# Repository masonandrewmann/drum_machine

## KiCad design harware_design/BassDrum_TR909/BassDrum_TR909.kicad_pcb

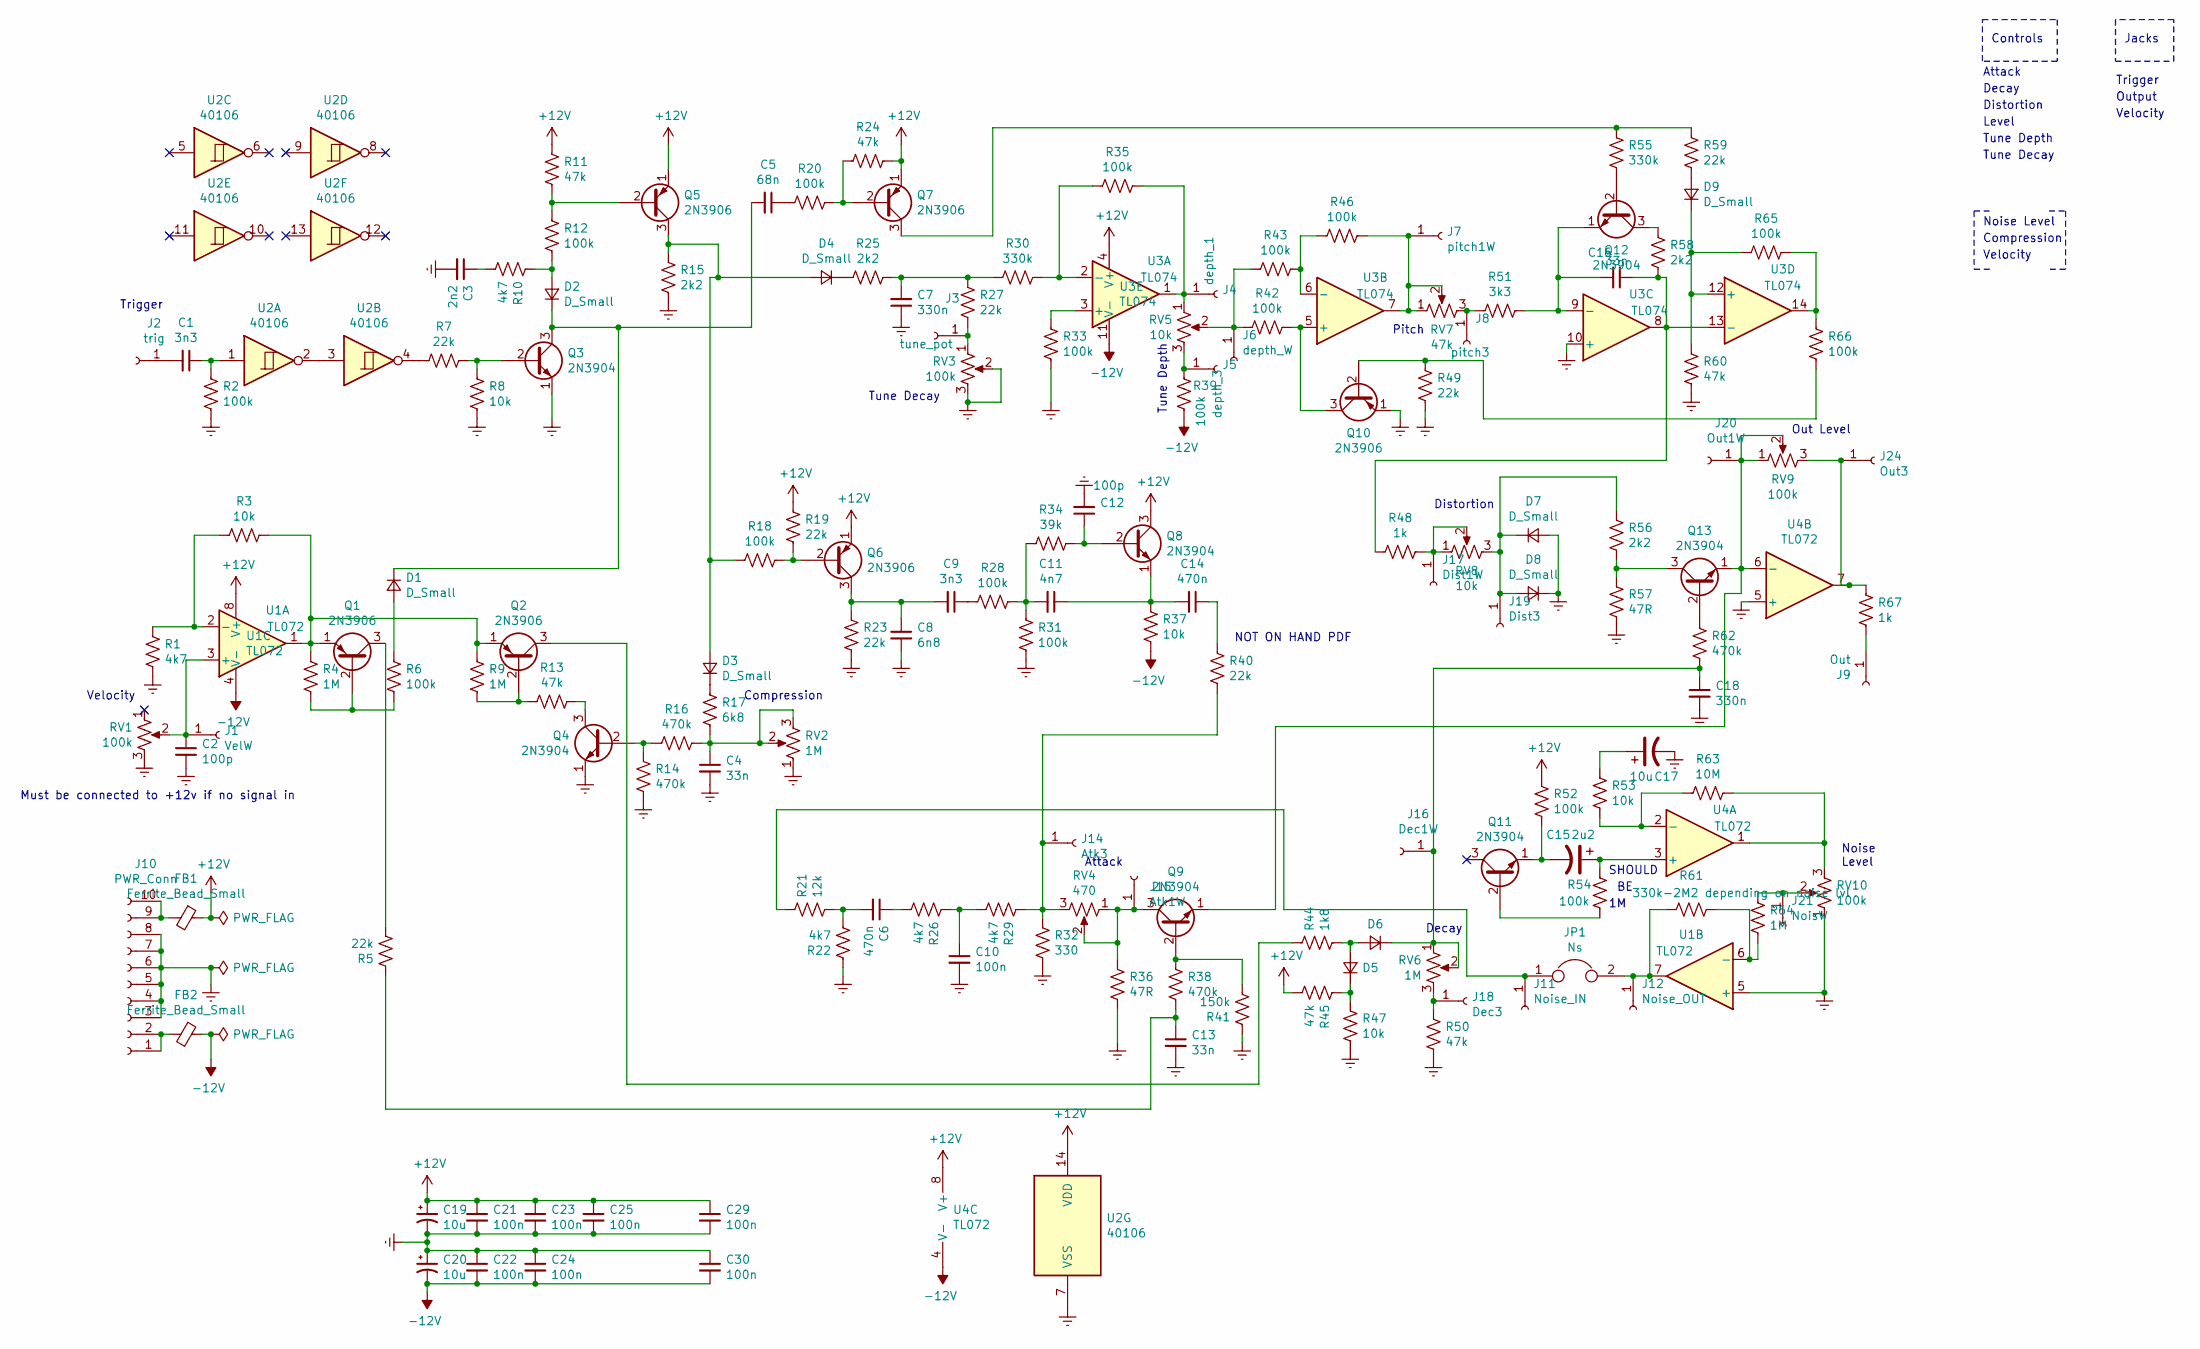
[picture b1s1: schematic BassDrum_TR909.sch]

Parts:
C1, C9: 3n3; C_0603_1608Metric_Pad1.05x0.95mm_HandSolder
C2, C12: 100p; C_0603_1608Metric_Pad1.05x0.95mm_HandSolder
C3: 2n2; C_0603_1608Metric_Pad1.05x0.95mm_HandSolder
C4, C13, C16: 33n; C_0603_1608Metric_Pad1.05x0.95mm_HandSolder
C5: 68n; C_0603_1608Metric_Pad1.05x0.95mm_HandSolder
C6, C14: 470n; C_0603_1608Metric_Pad1.05x0.95mm_HandSolder
C7, C18: 330n; C_0603_1608Metric_Pad1.05x0.95mm_HandSolder
C8: 6n8; C_0603_1608Metric_Pad1.05x0.95mm_HandSolder
C10, C21, C22, C23, C24, C25, C29, C30: 100n; C_0603_1608Metric_Pad1.05x0.95mm_HandSolder
C11: 4n7; C_0603_1608Metric_Pad1.05x0.95mm_HandSolder
C15: 2u2; C_0603_1608Metric_Pad1.05x0.95mm_HandSolder
C17, C19, C20: 10u; CP_Elec_5x5.4
D1, D2, D3, D4, D5, D6, D7, D8, D9: D_Small; D_SOD-323
FB1, FB2: Ferrite_Bead_Small; L_Axial_L7.0mm_D3.3mm_P2.54mm_Vertical_Fastron_MICC
J1: VelW; SolderWirePad_1x01_Drill1mm
J2: trig; SolderWirePad_1x01_Drill1mm
J3: tune_pot; SolderWirePad_1x01_Drill1mm
J4: depth_1; SolderWirePad_1x01_Drill1mm
J5: depth_3; SolderWirePad_1x01_Drill1mm
J6: depth_W; SolderWirePad_1x01_Drill1mm
J7: pitch1W; SolderWirePad_1x01_Drill1mm
J8: pitch3; SolderWirePad_1x01_Drill1mm
J9: Out; SolderWirePad_1x01_Drill1mm
J10: PWR_Conn; IDC-Header_2x05_P2.54mm_Vertical
J11: Noise_IN; SolderWirePad_1x01_Drill1mm
J12: Noise_OUT; SolderWirePad_1x01_Drill1mm
J14: Atk3; SolderWirePad_1x01_Drill1mm
J15: Atk1W; SolderWirePad_1x01_Drill1mm
J16: Dec1W; SolderWirePad_1x01_Drill1mm
J17: Dist1W; SolderWirePad_1x01_Drill1mm
J18: Dec3; SolderWirePad_1x01_Drill1mm
J19: Dist3; SolderWirePad_1x01_Drill1mm
J20: Out1W; SolderWirePad_1x01_Drill1mm
J21: NoisW; SolderWirePad_1x01_Drill1mm
J24: Out3; SolderWirePad_1x01_Drill1mm
JP1: Ns; SolderJumper-2_P1.3mm_Open_RoundedPad1.0x1.5mm
Q1, Q2, Q5, Q6, Q7, Q10: 2N3906; TSOT-23_HandSoldering
Q3, Q4, Q8, Q9, Q11, Q12, Q13: 2N3904; TSOT-23_HandSoldering
R1, R10, R22, R26, R29: 4k7; R_0603_1608Metric_Pad1.05x0.95mm_HandSolder
R2, R6, R12, R18, R20, R28, R31, R33, R35, R39, R42, R43, R46, R52, R54, R65, R66: 100k; R_0603_1608Metric_Pad1.05x0.95mm_HandSolder
R3, R8, R37, R47, R53: 10k; R_0603_1608Metric_Pad1.05x0.95mm_HandSolder
R4, R9, R64: 1M; R_0603_1608Metric_Pad1.05x0.95mm_HandSolder
R5, R7, R19, R23, R27, R40, R49, R59: 22k; R_0603_1608Metric_Pad1.05x0.95mm_HandSolder
R11, R13, R24, R45, R50, R60: 47k; R_0603_1608Metric_Pad1.05x0.95mm_HandSolder
R14, R16, R38, R62: 470k; R_0603_1608Metric_Pad1.05x0.95mm_HandSolder
R15, R25, R56, R58: 2k2; R_0603_1608Metric_Pad1.05x0.95mm_HandSolder
R17: 6k8; R_0603_1608Metric_Pad1.05x0.95mm_HandSolder
R21: 12k; R_0603_1608Metric_Pad1.05x0.95mm_HandSolder
R30, R55: 330k; R_0603_1608Metric_Pad1.05x0.95mm_HandSolder
R32: 330; R_0603_1608Metric_Pad1.05x0.95mm_HandSolder
R34: 39k; R_0603_1608Metric_Pad1.05x0.95mm_HandSolder
R36, R57: 47R; R_0603_1608Metric_Pad1.05x0.95mm_HandSolder
R41: 150k; R_0603_1608Metric_Pad1.05x0.95mm_HandSolder
R44: 1k8; R_0603_1608Metric_Pad1.05x0.95mm_HandSolder
R48, R67: 1k; R_0603_1608Metric_Pad1.05x0.95mm_HandSolder
R51: 3k3; R_0603_1608Metric_Pad1.05x0.95mm_HandSolder
R61: 330k-2M2 depending on noise lvl; R_Axial_DIN0207_L6.3mm_D2.5mm_P7.62mm_Horizontal
R63: 10M; R_0603_1608Metric_Pad1.05x0.95mm_HandSolder
RV1, RV3, RV9: 100k
RV2: 1M; Potentiometer_Runtron_RM-065_Vertical
RV4: 470
RV5, RV8: 10k
RV6: 1M
RV7: 47k
RV10: 100k; Potentiometer_Runtron_RM-065_Vertical
U1, U4: TL072; SOIC-8_3.9x4.9mm_P1.27mm
U2: 40106; SOIC-14_3.9x8.7mm_P1.27mm
U3: TL074; SOIC-14_3.9x8.7mm_P1.27mm

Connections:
+12V: C19.1, C21.1, C23.1, C25.1, C29.1, FB1.1, Q5.1 (E), Q6.1 (E), Q7.1 (E), Q8.3 (C), R11.2, R19.2, R24.2, R45.2, R52.2, U1.8 (V+), U2.14 (VDD), U3.4 (V+), U4.8 (V+)
-12V: C20.2, C22.2, C24.2, C30.2, FB2.1, R37.2, R39.1, U1.4 (V-), U3.11 (V-), U4.4 (V-)
Earth: C2.2, C3.2, C4.2, C7.1, C8.2, C10.2, C12.2, C13.2, C17.2, C18.2, C19.2, C20.1, C21.2, C22.1, C23.2, C24.1, C25.2, C29.2, C30.1, D7.2 (A), D8.1 (K), J10.3, J10.4, J10.5, J10.6, J10.7, J10.8, Q3.1 (E), Q4.1 (E), Q10.1 (E), R1.1, R2.1, R8.1, R14.2, R15.1, R22.1, R23.1, R31.2, R32.2, R33.1, R36.2, R41.1, R47.2, R49.2, R50.2, R57.2, R60.2, RV1.3, RV2.1, RV3.2, RV3.3, RV10.1, U1.5 (+), U2.7 (VSS), U3.10 (+), U4.5 (+)
unnamed: C1.1, R2.2, U2.1
unnamed: C1.2, J2.1
unnamed: C2.1, J1.1, RV1.2, U1.3 (+)
unnamed: C3.1, R10.1
unnamed: C4.1, R16.1, R17.1, RV2.2, RV2.3
unnamed: C5.1, R20.1
unnamed: C5.2, D1.1 (K), D2.1 (K), Q3.3 (C)
unnamed: C6.1, R26.2
unnamed: C6.2, R21.2, R22.2
unnamed: C7.2, R25.2, R27.1, R30.2
unnamed: C8.1, C9.2, Q6.3 (C), R23.2
unnamed: C9.1, R28.1
unnamed: C10.1, R26.1, R29.2
unnamed: C11.1, C14.2, Q8.1 (E), R37.1
unnamed: C11.2, R28.2, R31.1, R34.1
unnamed: C12.1, Q8.2 (B), R34.2
unnamed: C13.1, R5.1, R38.2
unnamed: C14.1, R40.1
unnamed: C15.1, R54.2, U4.3 (+)
unnamed: C15.2, Q11.1 (E), R52.1
unnamed: C16.1, R48.1, R58.2, U3.8, U3.13 (-)
unnamed: C16.2, Q12.1 (E), R51.2, U3.9 (-)
unnamed: C17.1, R53.2
unnamed: C18.1, D6.1 (K), J16.1, R62.2, RV6.1, RV6.2
unnamed: D1.2 (A), R6.2
unnamed: D2.2 (A), R10.2, R12.1
unnamed: D3.1 (K), R17.2
unnamed: D3.2 (A), D4.2 (A), Q5.3 (C), R15.2, R18.2
unnamed: D4.1 (K), R25.1
unnamed: D5.1 (K), R45.1, R47.1
unnamed: D5.2 (A), D6.2 (A), R44.2
unnamed: D7.1 (K), D8.2 (A), J19.1, R56.1, RV8.3
unnamed: D9.1 (K), R60.1, R65.2, U3.12 (+)
unnamed: D9.2 (A), R59.2
unnamed: FB1.2, J10.9, J10.10
unnamed: FB2.2, J10.1, J10.2
unnamed: J3.1, R27.2, RV3.1
unnamed: J4.1, R35.1, RV5.1, U3.1
unnamed: J5.1, R39.2, RV5.3
unnamed: J6.1, R42.1, R43.1, RV5.2
unnamed: J7.1, R46.2, RV7.1, RV7.2, U3.7
unnamed: J8.1, R51.1, RV7.3
unnamed: J9.1, R67.2
unnamed: J11.1, JP1.1, R21.1
unnamed: J12.1, JP1.2, R61.1, U1.7
unnamed: J14.1, R29.1, R32.1, R40.2, RV4.3
unnamed: J15.1, Q9.3 (C), R36.1, RV4.1, RV4.2
unnamed: J17.1, R48.2, RV8.1, RV8.2
unnamed: J18.1, R50.1, RV6.3
unnamed: J20.1, Q9.1 (E), Q13.1 (E), RV9.1, RV9.2, U4.6 (-)
unnamed: J21.1, R64.2, RV10.2
unnamed: J24.1, R67.1, RV9.3, U4.7
unnamed: Q1.1 (E), Q2.1 (E), R3.1, R4.2, R9.2, U1.1
unnamed: Q1.2 (B), R4.1, R6.1
unnamed: Q1.3 (C), R5.2
unnamed: Q2.2 (B), R9.1, R13.1
unnamed: Q2.3 (C), R44.1
unnamed: Q3.2 (B), R7.1, R8.2
unnamed: Q4.2 (B), R14.1, R16.2
unnamed: Q4.3 (C), R13.2
unnamed: Q5.2 (B), R11.1, R12.2
unnamed: Q6.2 (B), R18.1, R19.1
unnamed: Q7.2 (B), R20.2, R24.1
unnamed: Q7.3 (C), R55.1, R59.1
unnamed: Q9.2 (B), R38.1, R41.2
unnamed: Q10.2 (B), R49.1, R66.1
unnamed: Q10.3 (C), R42.2, U3.5 (+)
unnamed: Q11.2 (B), R54.1
unnamed: Q12.2 (B), R55.2
unnamed: Q12.3 (C), R58.1
unnamed: Q13.2 (B), R62.1
unnamed: Q13.3 (C), R56.2, R57.1
unnamed: R1.2, R3.2, U1.2 (-)
unnamed: R7.2, U2.4
unnamed: R30.1, R35.2, U3.2 (-)
unnamed: R33.2, U3.3 (+)
unnamed: R43.2, R46.1, U3.6 (-)
unnamed: R53.1, R63.2, U4.2 (-)
unnamed: R61.2, R64.1, U1.6 (-)
unnamed: R63.1, RV10.3, U4.1
unnamed: R65.1, R66.2, U3.14
unnamed: U2.2, U2.3

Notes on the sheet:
Tune Decay
Tune Depth
Pitch
Distortion
Out Level
Compression
Attack
Decay
Noise Level
Velocity
Trigger
Must be connected to +12v if no signal in
NOT ON HAND PDF
Controls
Attack
Decay
Distortion
Level
Tune Decay
Noise Level
Jacks
Output
SHOULD

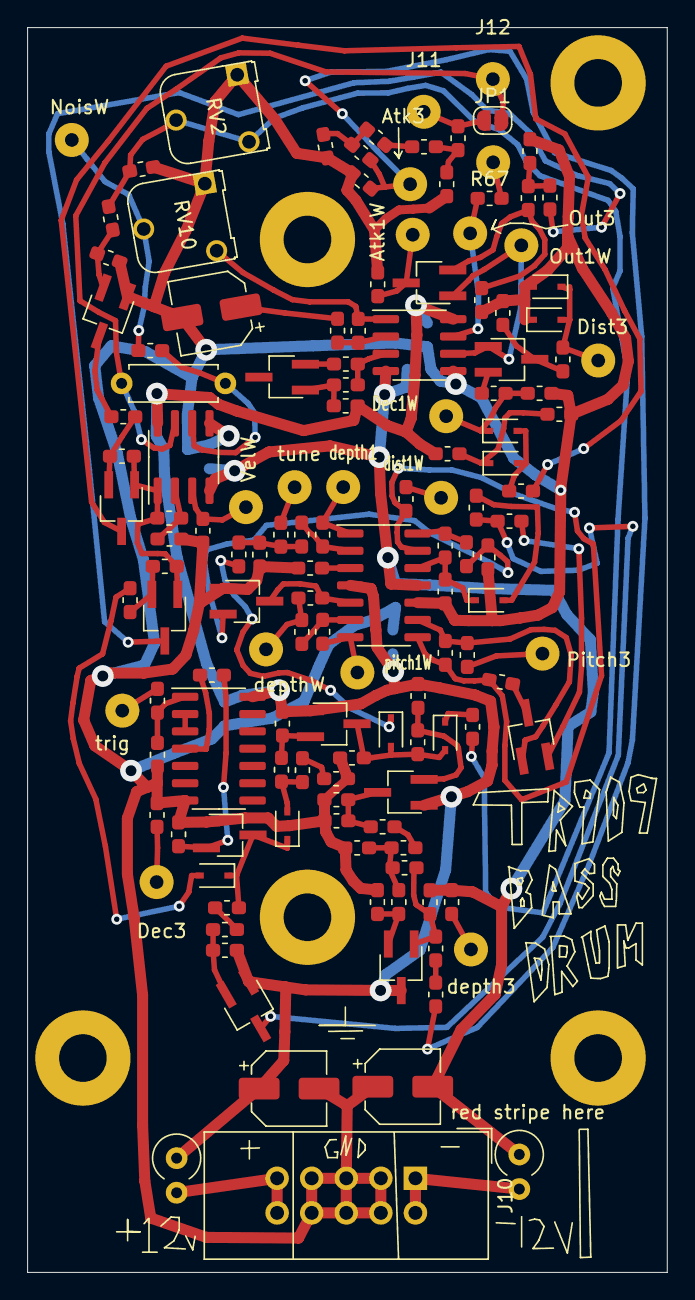
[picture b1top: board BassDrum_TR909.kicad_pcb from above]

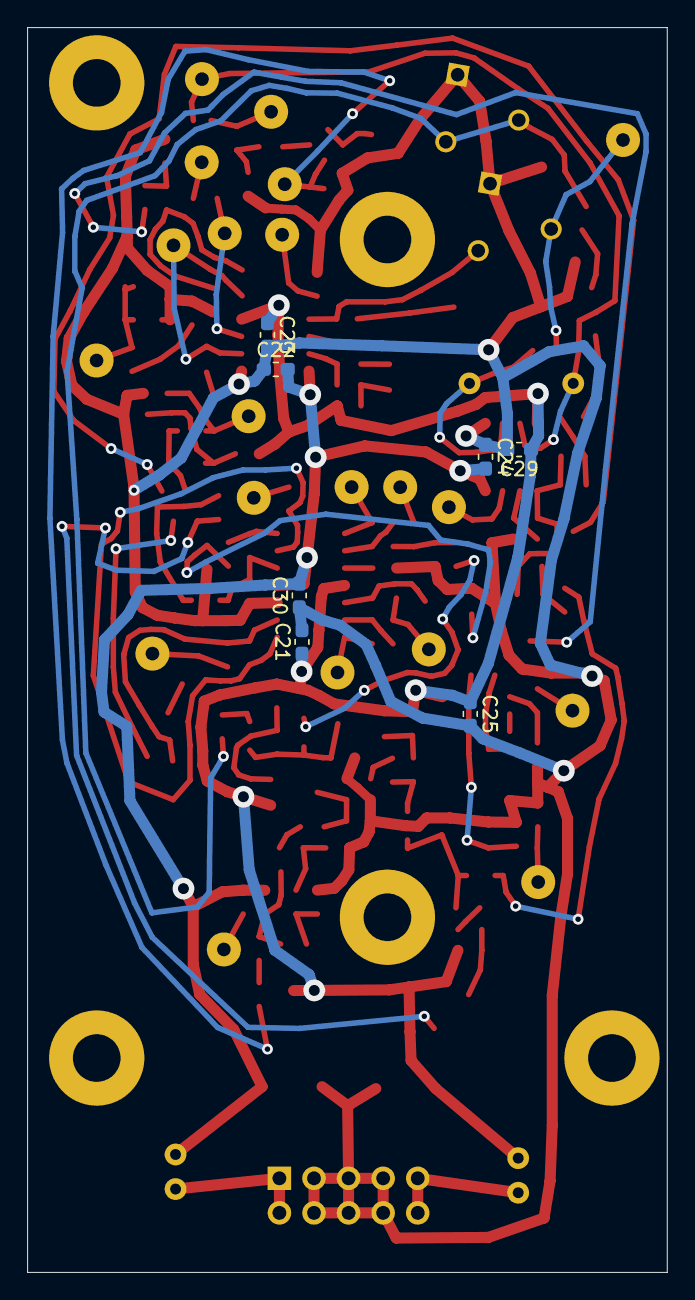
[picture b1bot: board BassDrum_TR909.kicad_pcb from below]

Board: 2 copper layers, 47.0 x 91.4 mm, 146 parts (7 on the bottom side), 85 nets.

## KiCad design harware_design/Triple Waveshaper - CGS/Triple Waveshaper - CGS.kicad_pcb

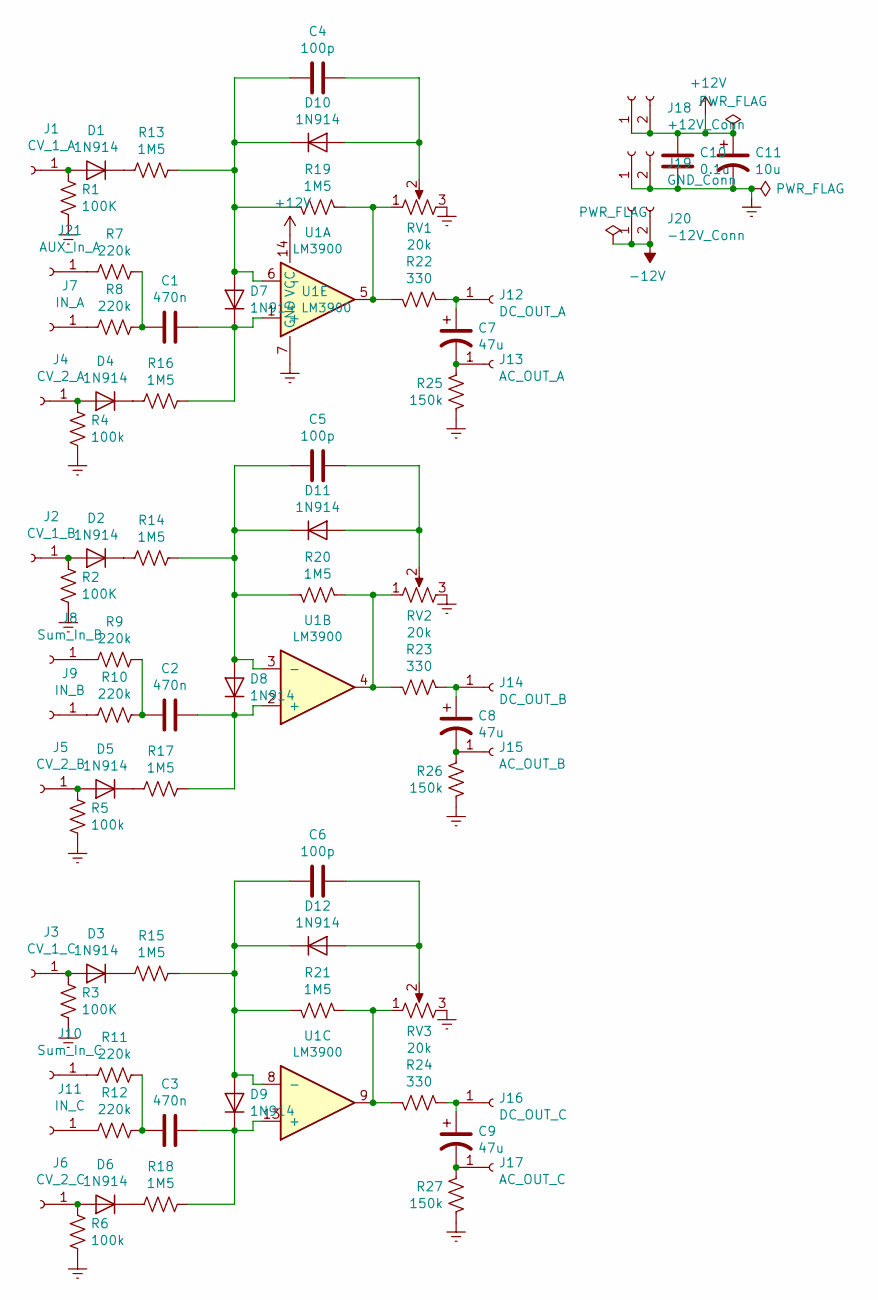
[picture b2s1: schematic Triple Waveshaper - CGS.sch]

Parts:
C1, C2, C3: 470n; C_Rect_L7.0mm_W2.5mm_P5.00mm
C4, C5, C6: 100p; C_Rect_L7.0mm_W2.5mm_P5.00mm
C7, C8, C9: 47u; CP_Radial_D4.0mm_P2.00mm
C10: 0.1u; C_Rect_L7.0mm_W2.5mm_P5.00mm
C11: 10u; CP_Radial_D4.0mm_P2.00mm
D1, D2, D3, D4, D5, D6, D7, D8, D9, D10, D11, D12: 1N914; D_T-1_P5.08mm_Horizontal
J1: CV_1_A; SolderWirePad_1x01_Drill1mm
J2: CV_1_B; SolderWirePad_1x01_Drill1mm
J3: CV_1_C; SolderWirePad_1x01_Drill1mm
J4: CV_2_A; SolderWirePad_1x01_Drill1mm
J5: CV_2_B; SolderWirePad_1x01_Drill1mm
J6: CV_2_C; SolderWirePad_1x01_Drill1mm
J7: IN_A; SolderWirePad_1x01_Drill1mm
J8: Sum_In_B; SolderWirePad_1x01_Drill1mm
J9: IN_B; SolderWirePad_1x01_Drill1mm
J10: Sum_In_C; SolderWirePad_1x01_Drill1mm
J11: IN_C; SolderWirePad_1x01_Drill1mm
J12: DC_OUT_A; SolderWirePad_1x01_Drill1mm
J13: AC_OUT_A; SolderWirePad_1x01_Drill1mm
J14: DC_OUT_B; SolderWirePad_1x01_Drill1mm
J15: AC_OUT_B; SolderWirePad_1x01_Drill1mm
J16: DC_OUT_C; SolderWirePad_1x01_Drill1mm
J17: AC_OUT_C; SolderWirePad_1x01_Drill1mm
J18: +12V_Conn; SolderWirePad_1x02_P3.81mm_Drill1mm
J19: GND_Conn; SolderWirePad_1x02_P3.81mm_Drill1mm
J20: -12V_Conn; SolderWirePad_1x02_P3.81mm_Drill1mm
J21: AUX_In_A; SolderWirePad_1x01_Drill1mm
R1, R2, R3: 100K; R_Axial_DIN0207_L6.3mm_D2.5mm_P7.62mm_Horizontal
R4, R5, R6: 100k; R_Axial_DIN0207_L6.3mm_D2.5mm_P7.62mm_Horizontal
R7, R8, R9, R10, R11, R12: 220k; R_Axial_DIN0207_L6.3mm_D2.5mm_P7.62mm_Horizontal
R13, R14, R15, R16, R17, R18, R19, R20, R21: 1M5; R_Axial_DIN0207_L6.3mm_D2.5mm_P7.62mm_Horizontal
R22, R23, R24: 330; R_Axial_DIN0207_L6.3mm_D2.5mm_P7.62mm_Horizontal
R25, R26, R27: 150k; R_Axial_DIN0207_L6.3mm_D2.5mm_P7.62mm_Horizontal
RV1, RV2, RV3: 20k; Potentiometer_Runtron_RM-065_Vertical
U1: LM3900; DIP-14_W7.62mm_Socket

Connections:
+12V: C10.1, C11.1, J18.1, J18.2, U1.14 (VCC)
-12V: J20.1, J20.2
Earth: C10.2, C11.2, J19.1, J19.2, R1.1, R2.1, R3.1, R4.1, R5.1, R6.1, R25.1, R26.1, R27.1, RV1.3, RV2.3, RV3.3, U1.7 (GND)
unnamed: C1.1, R7.1, R8.1
unnamed: C1.2, D7.1 (K), R16.1, U1.1 (+)
unnamed: C2.1, R9.1, R10.1
unnamed: C2.2, D8.1 (K), R17.1, U1.2 (+)
unnamed: C3.1, R11.1, R12.1
unnamed: C3.2, D9.1 (K), R18.1, U1.13 (+)
unnamed: C4.1, D7.2 (A), D10.1 (K), R13.1, R19.2, U1.6 (-)
unnamed: C4.2, D10.2 (A), RV1.2
unnamed: C5.1, D8.2 (A), D11.1 (K), R14.1, R20.2, U1.3 (-)
unnamed: C5.2, D11.2 (A), RV2.2
unnamed: C6.1, D9.2 (A), D12.1 (K), R15.1, R21.2, U1.8 (-)
unnamed: C6.2, D12.2 (A), RV3.2
unnamed: C7.1, J12.1, R22.1
unnamed: C7.2, J13.1, R25.2
unnamed: C8.1, J14.1, R23.1
unnamed: C8.2, J15.1, R26.2
unnamed: C9.1, J16.1, R24.1
unnamed: C9.2, J17.1, R27.2
unnamed: D1.1 (K), R13.2
unnamed: D1.2 (A), J1.1, R1.2
unnamed: D2.1 (K), R14.2
unnamed: D2.2 (A), J2.1, R2.2
unnamed: D3.1 (K), R15.2
unnamed: D3.2 (A), J3.1, R3.2
unnamed: D4.1 (K), R16.2
unnamed: D4.2 (A), J4.1, R4.2
unnamed: D5.1 (K), R17.2
unnamed: D5.2 (A), J5.1, R5.2
unnamed: D6.1 (K), R18.2
unnamed: D6.2 (A), J6.1, R6.2
unnamed: J7.1, R8.2
unnamed: J8.1, R9.2
unnamed: J9.1, R10.2
unnamed: J10.1, R11.2
unnamed: J11.1, R12.2
unnamed: J21.1, R7.2
unnamed: R19.1, R22.2, RV1.1, U1.5
unnamed: R20.1, R23.2, RV2.1, U1.4
unnamed: R21.1, R24.2, RV3.1, U1.9

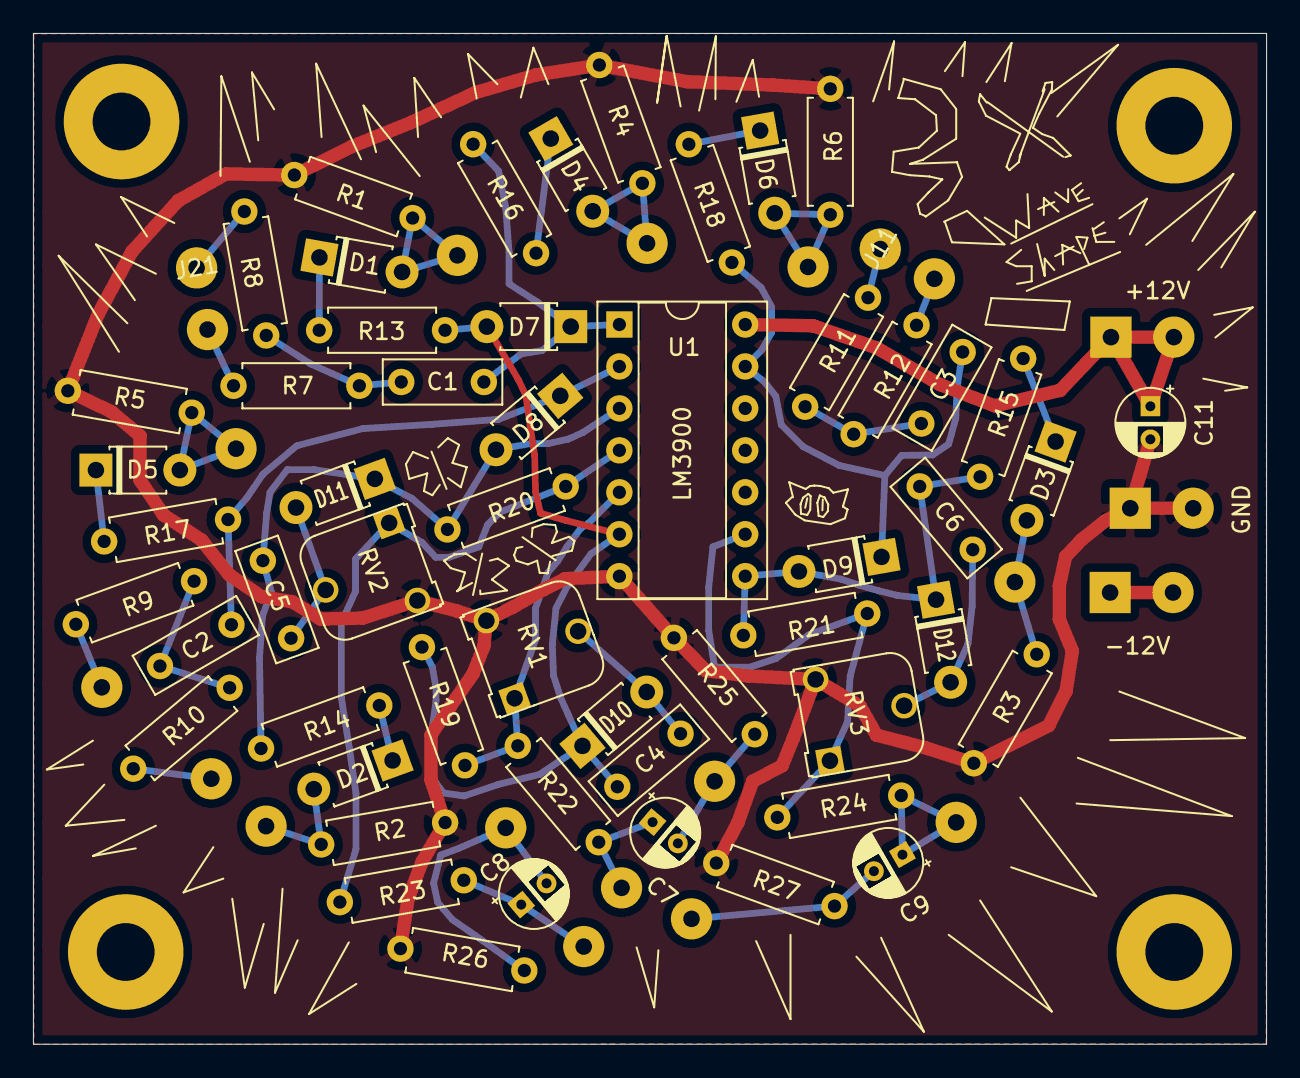
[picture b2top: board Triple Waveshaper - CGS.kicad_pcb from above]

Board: 2 copper layers, 74.7 x 61.2 mm, 74 parts (0 on the bottom side), 42 nets.

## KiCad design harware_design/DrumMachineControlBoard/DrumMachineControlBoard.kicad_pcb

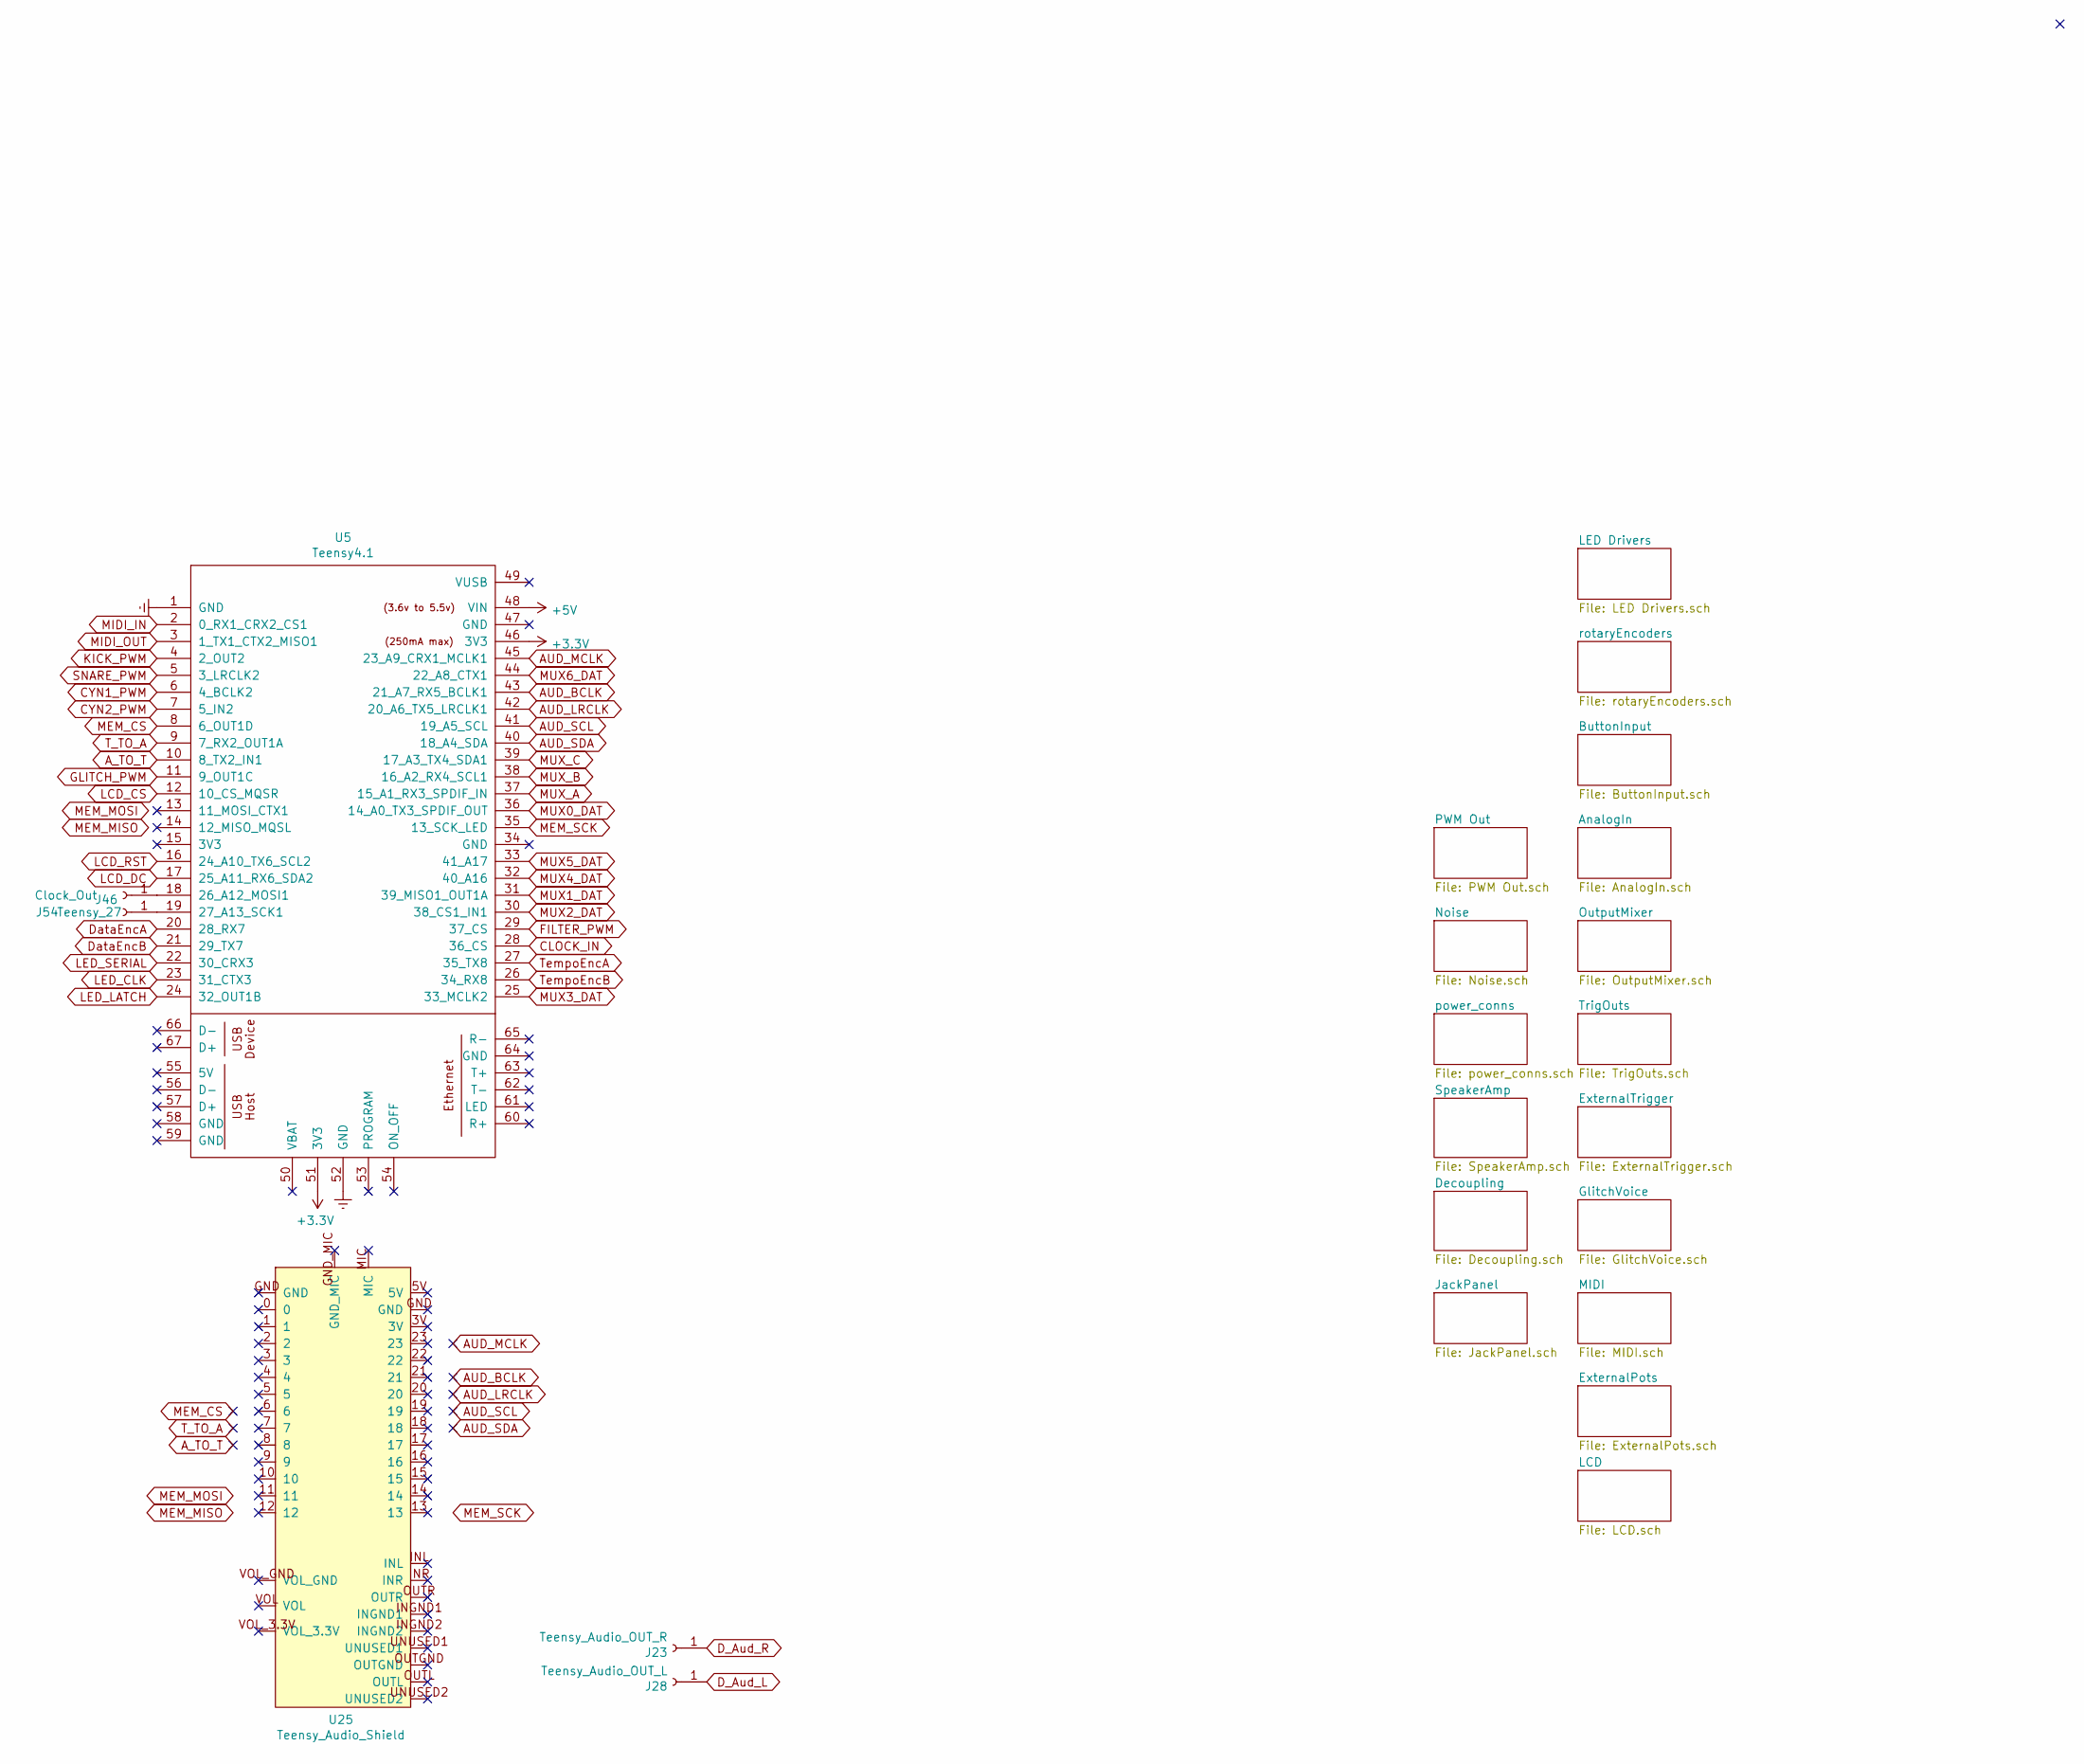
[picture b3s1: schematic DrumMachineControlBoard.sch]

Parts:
J23: Teensy_Audio_OUT_R; SolderWirePad_1x01_Drill1mm
J28: Teensy_Audio_OUT_L; SolderWirePad_1x01_Drill1mm
J46: Clock_Out; SolderWirePad_1x01_Drill1mm
J54: Teensy_27; SolderWirePad_1x01_Drill1mm
U5: Teensy4.1; Teensy41
U25: Teensy_Audio_Shield

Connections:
+3V3: U5.46 (3V3), U5.51 (3V3); also elsewhere on the board
+5V: U5.48 (VIN); also elsewhere on the board
AUD_BCLK: U5.43 (21_A7_RX5_BCLK1)
AUD_LRCLK: U5.42 (20_A6_TX5_LRCLK1)
AUD_MCLK: U5.45 (23_A9_CRX1_MCLK1)
AUD_SCL: U5.41 (19_A5_SCL)
AUD_SDA: U5.40 (18_A4_SDA)
A_TO_T: U5.10 (8_TX2_IN1)
CLOCK_IN: U5.28 (36_CS); also elsewhere on the board
CYN1_PWM: U5.6 (4_BCLK2); also elsewhere on the board
CYN2_PWM: U5.7 (5_IN2); also elsewhere on the board
D_Aud_L: J28.1; also elsewhere on the board
D_Aud_R: J23.1; also elsewhere on the board
DataEncA: U5.20 (28_RX7); also elsewhere on the board
DataEncB: U5.21 (29_TX7); also elsewhere on the board
FILTER_PWM: U5.29 (37_CS); also elsewhere on the board
GLITCH_PWM: U5.11 (9_OUT1C); also elsewhere on the board
KICK_PWM: U5.4 (2_OUT2); also elsewhere on the board
LCD_CS: U5.12 (10_CS_MQSR); also elsewhere on the board
LCD_DC: U5.17 (25_A11_RX6_SDA2); also elsewhere on the board
LCD_RST: U5.16 (24_A10_TX6_SCL2); also elsewhere on the board
LED_CLK: U5.23 (31_CTX3); also elsewhere on the board
LED_LATCH: U5.24 (32_OUT1B); also elsewhere on the board
LED_SERIAL: U5.22 (30_CRX3); also elsewhere on the board
MEM_CS: U5.8 (6_OUT1D)
MEM_SCK: U5.35 (13_SCK_LED); also elsewhere on the board
MIDI_IN: U5.2 (0_RX1_CRX2_CS1); also elsewhere on the board
MIDI_OUT: U5.3 (1_TX1_CTX2_MISO1); also elsewhere on the board
MUX0_DAT: U5.36 (14_A0_TX3_SPDIF_OUT); also elsewhere on the board
MUX1_DAT: U5.31 (39_MISO1_OUT1A); also elsewhere on the board
MUX2_DAT: U5.30 (38_CS1_IN1); also elsewhere on the board
MUX3_DAT: U5.25 (33_MCLK2); also elsewhere on the board
MUX4_DAT: U5.32 (40_A16); also elsewhere on the board
MUX5_DAT: U5.33 (41_A17); also elsewhere on the board
MUX6_DAT: U5.44 (22_A8_CTX1); also elsewhere on the board
MUX_A: U5.37 (15_A1_RX3_SPDIF_IN); also elsewhere on the board
MUX_B: U5.38 (16_A2_RX4_SCL1); also elsewhere on the board
MUX_C: U5.39 (17_A3_TX4_SDA1); also elsewhere on the board
unnamed: J46.1, U5.18 (26_A12_MOSI1)
unnamed: J54.1, U5.19 (27_A13_SCK1)
SNARE_PWM: U5.5 (3_LRCLK2); also elsewhere on the board
T_TO_A: U5.9 (7_RX2_OUT1A)
TempoEncA: U5.27 (35_TX8); also elsewhere on the board
TempoEncB: U5.26 (34_RX8); also elsewhere on the board

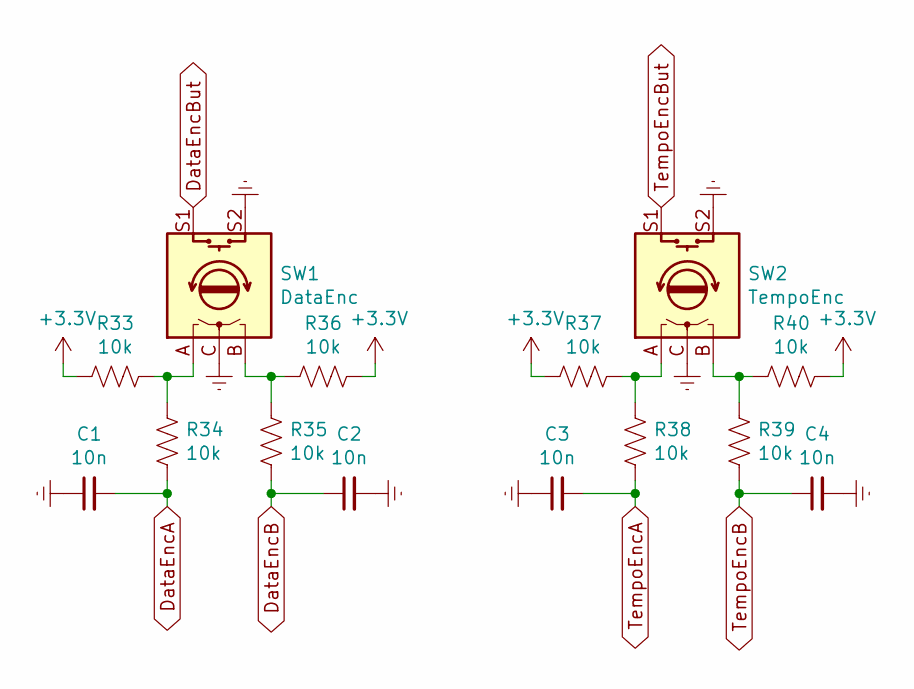
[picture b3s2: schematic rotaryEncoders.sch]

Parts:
C1, C2, C3, C4: 10n; C_0603_1608Metric_Pad1.05x0.95mm_HandSolder
R33, R34, R35, R36, R37, R38, R39, R40: 10k; R_0603_1608Metric_Pad1.05x0.95mm_HandSolder
SW1: DataEnc; RotaryEncoder_Alps_EC11E-Switch_Vertical_H20mm
SW2: TempoEnc; RotaryEncoder_Alps_EC11E-Switch_Vertical_H20mm

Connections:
+3V3: R33.2, R36.1, R37.2, R40.1; also elsewhere on the board
DataEncA: C1.2, R34.1; also elsewhere on the board
DataEncB: C2.1, R35.1; also elsewhere on the board
DataEncBut: SW1.S1; also elsewhere on the board
unnamed: R33.1, R34.2, SW1.A
unnamed: R35.2, R36.2, SW1.B
unnamed: R37.1, R38.2, SW2.A
unnamed: R39.2, R40.2, SW2.B
TempoEncA: C3.2, R38.1; also elsewhere on the board
TempoEncB: C4.1, R39.1; also elsewhere on the board
TempoEncBut: SW2.S1; also elsewhere on the board
